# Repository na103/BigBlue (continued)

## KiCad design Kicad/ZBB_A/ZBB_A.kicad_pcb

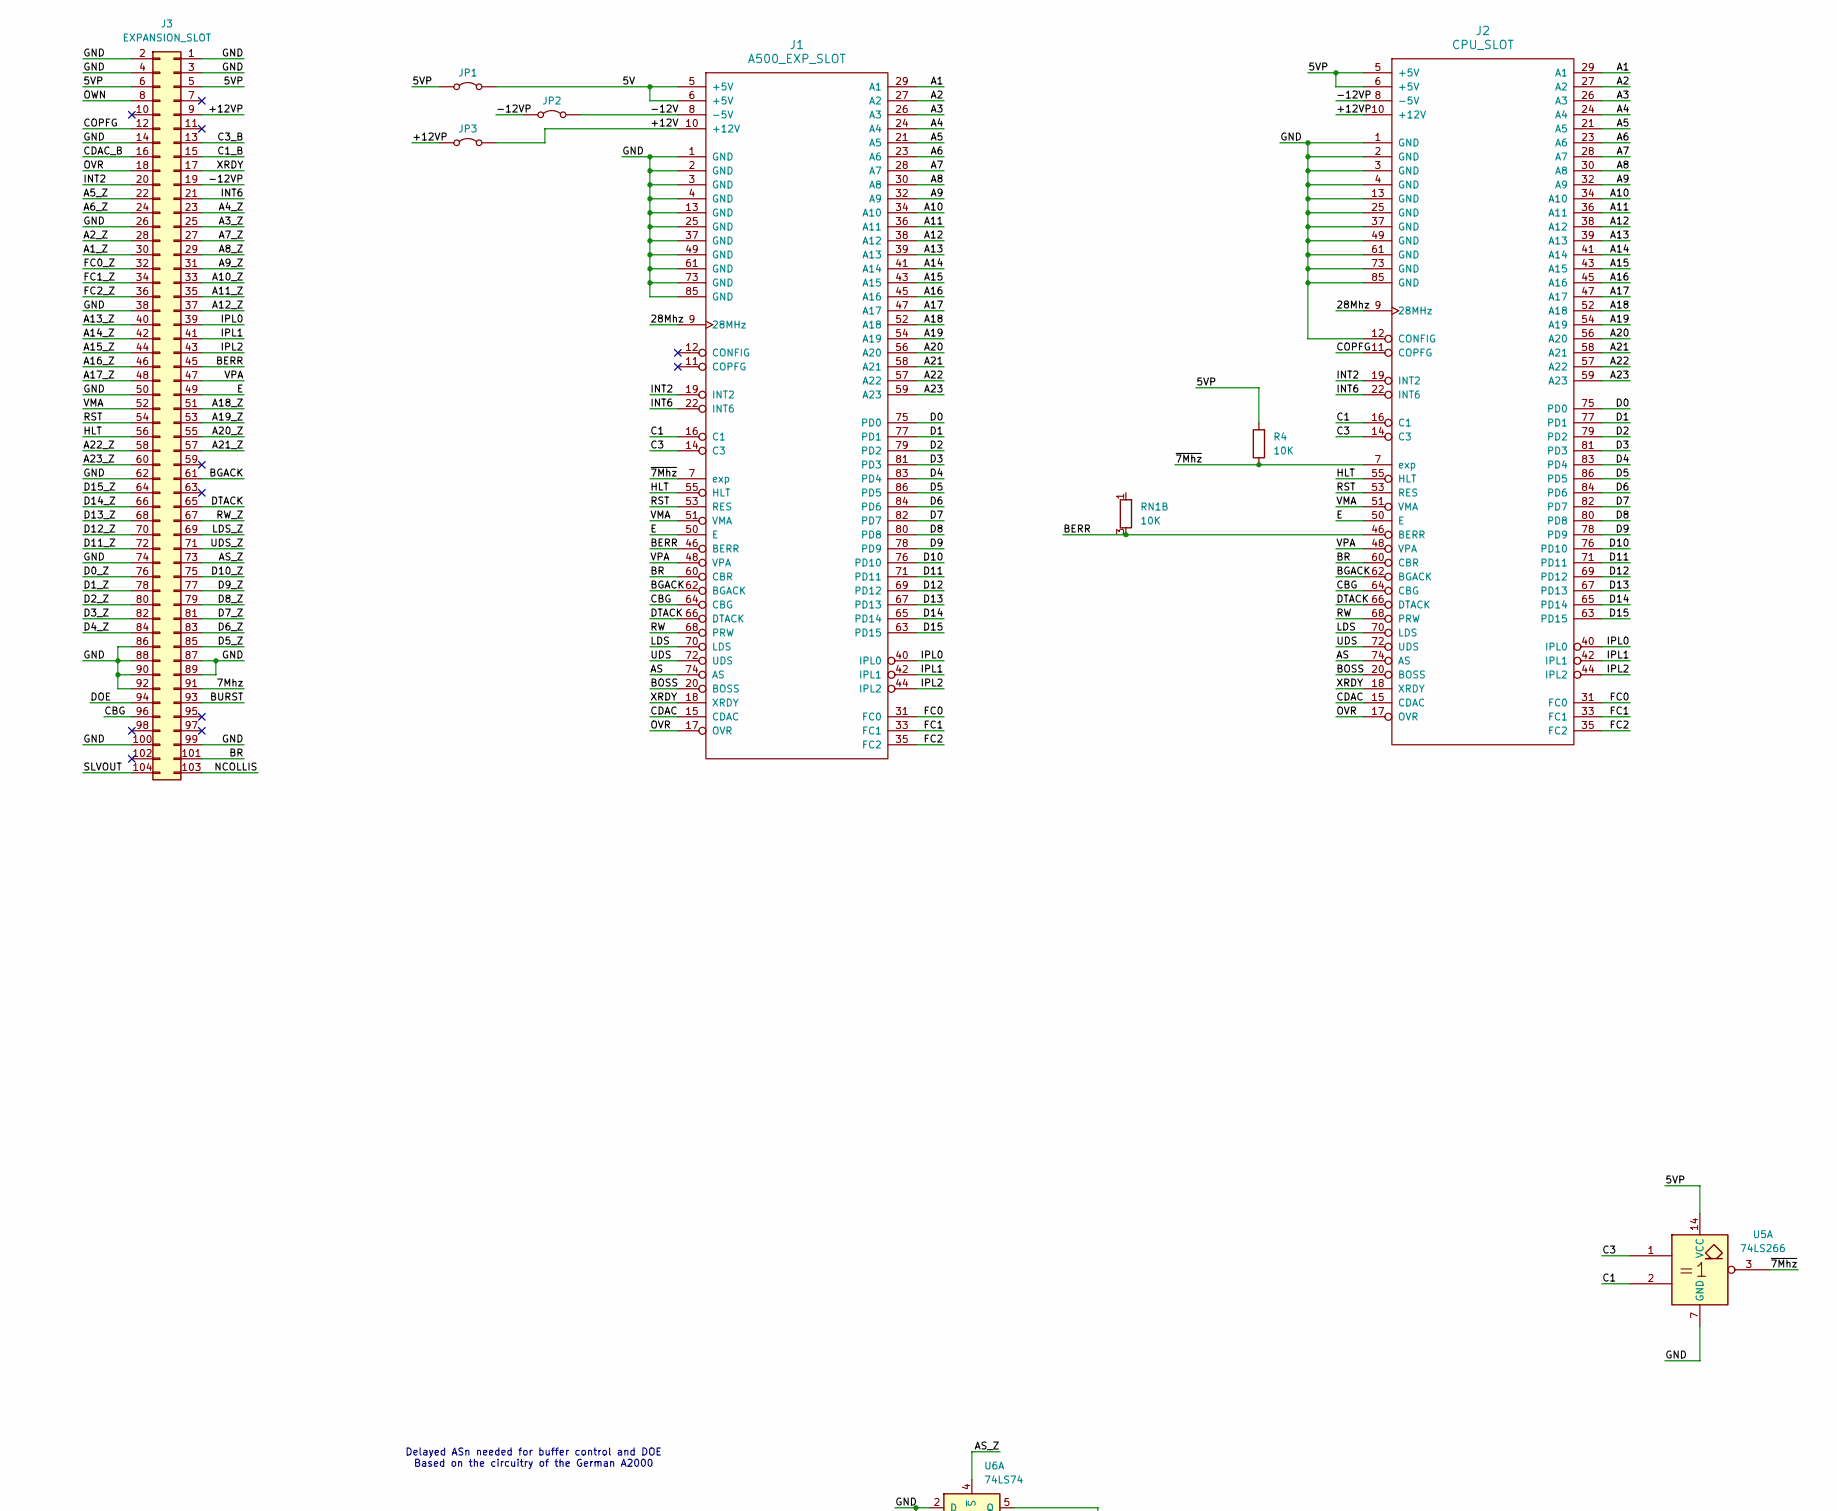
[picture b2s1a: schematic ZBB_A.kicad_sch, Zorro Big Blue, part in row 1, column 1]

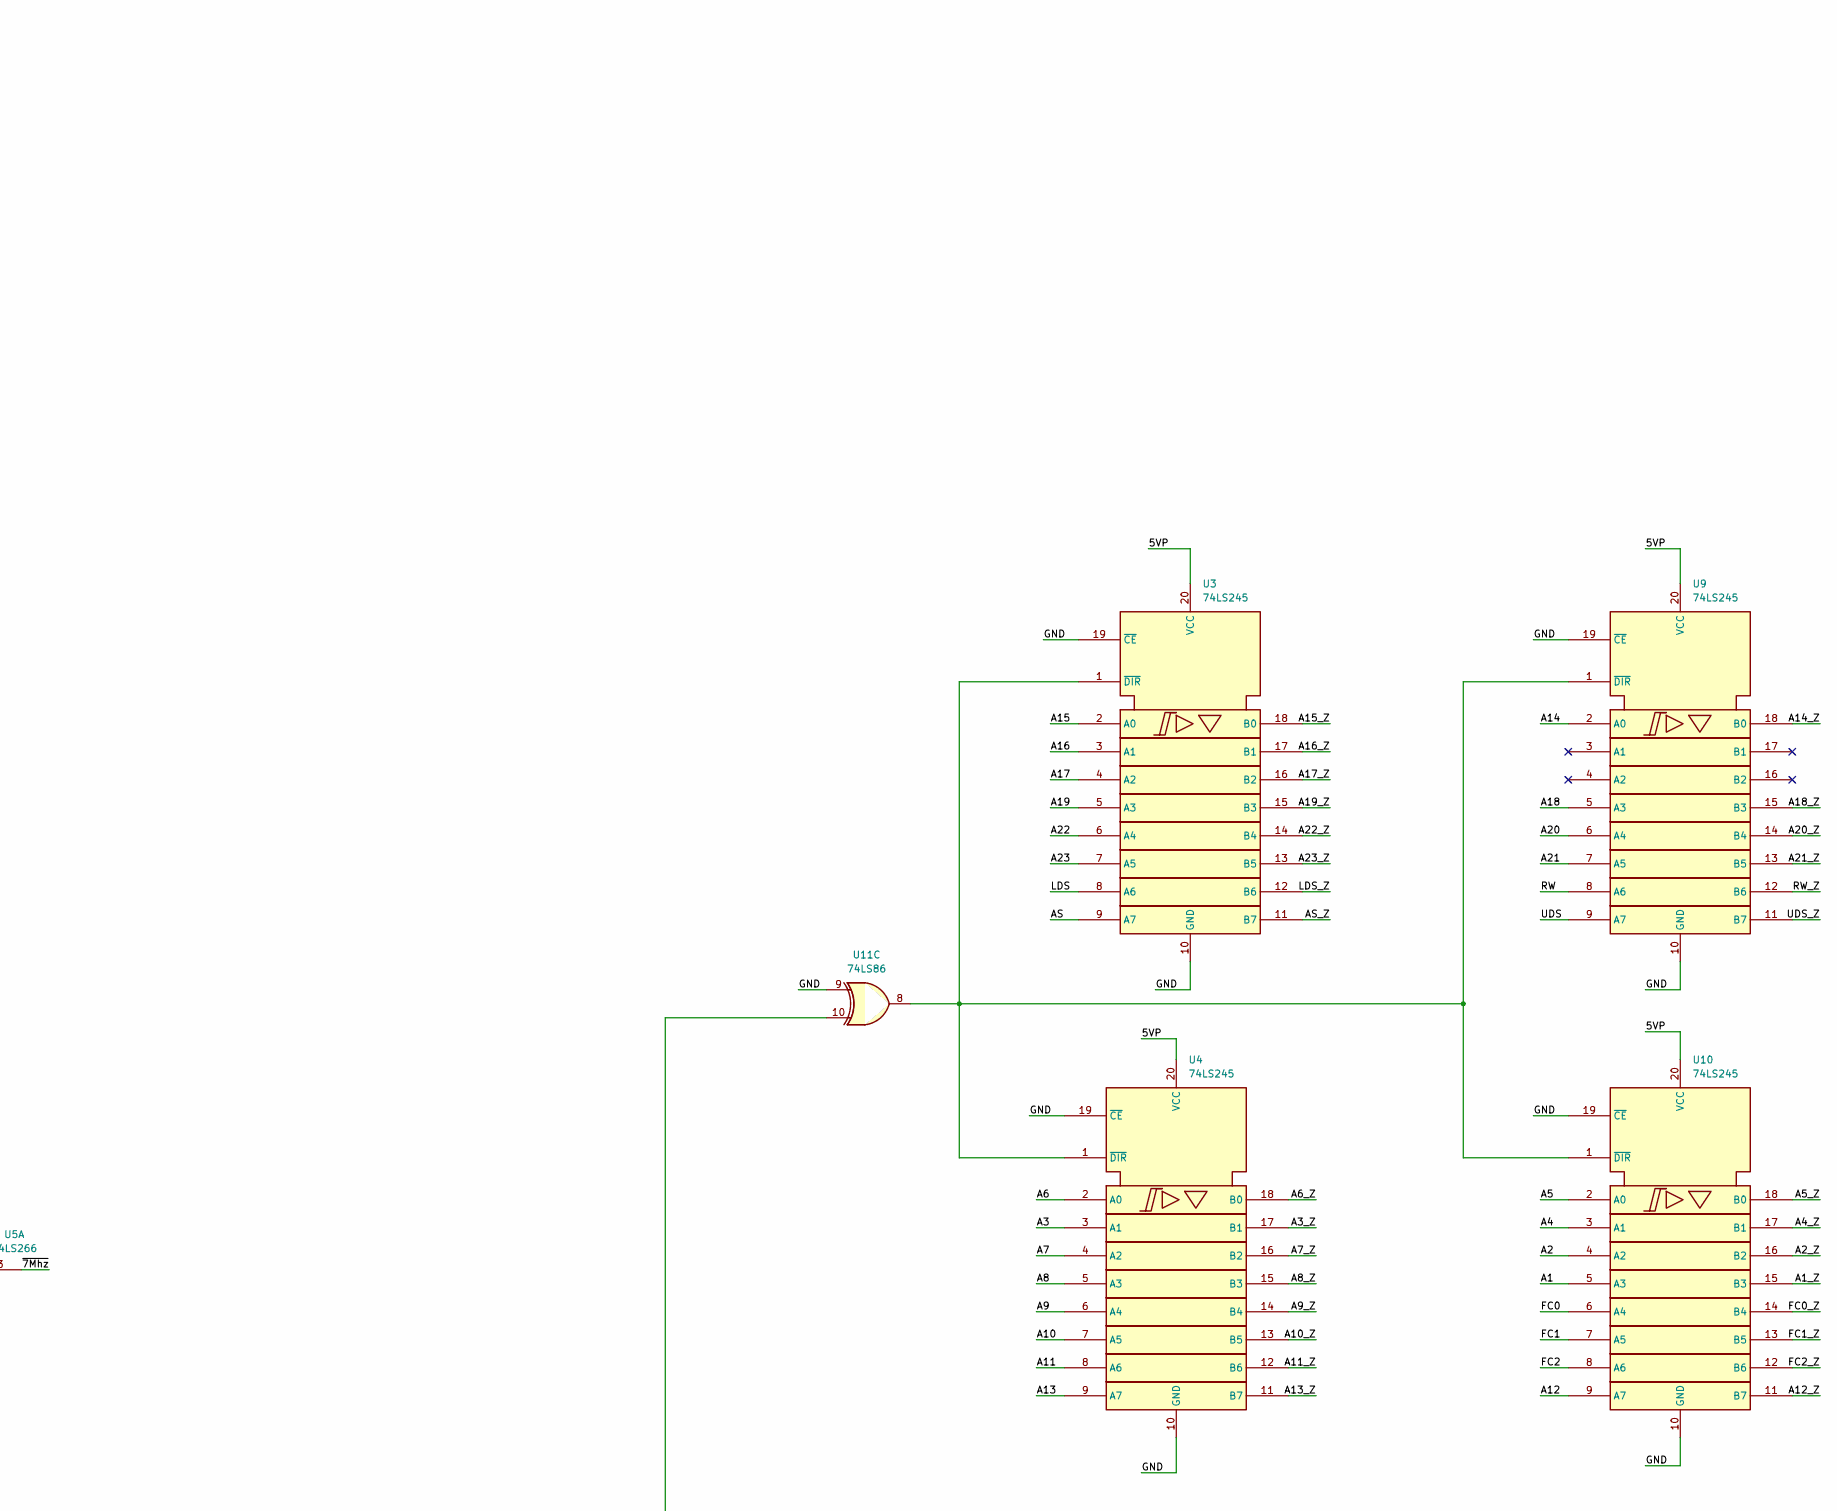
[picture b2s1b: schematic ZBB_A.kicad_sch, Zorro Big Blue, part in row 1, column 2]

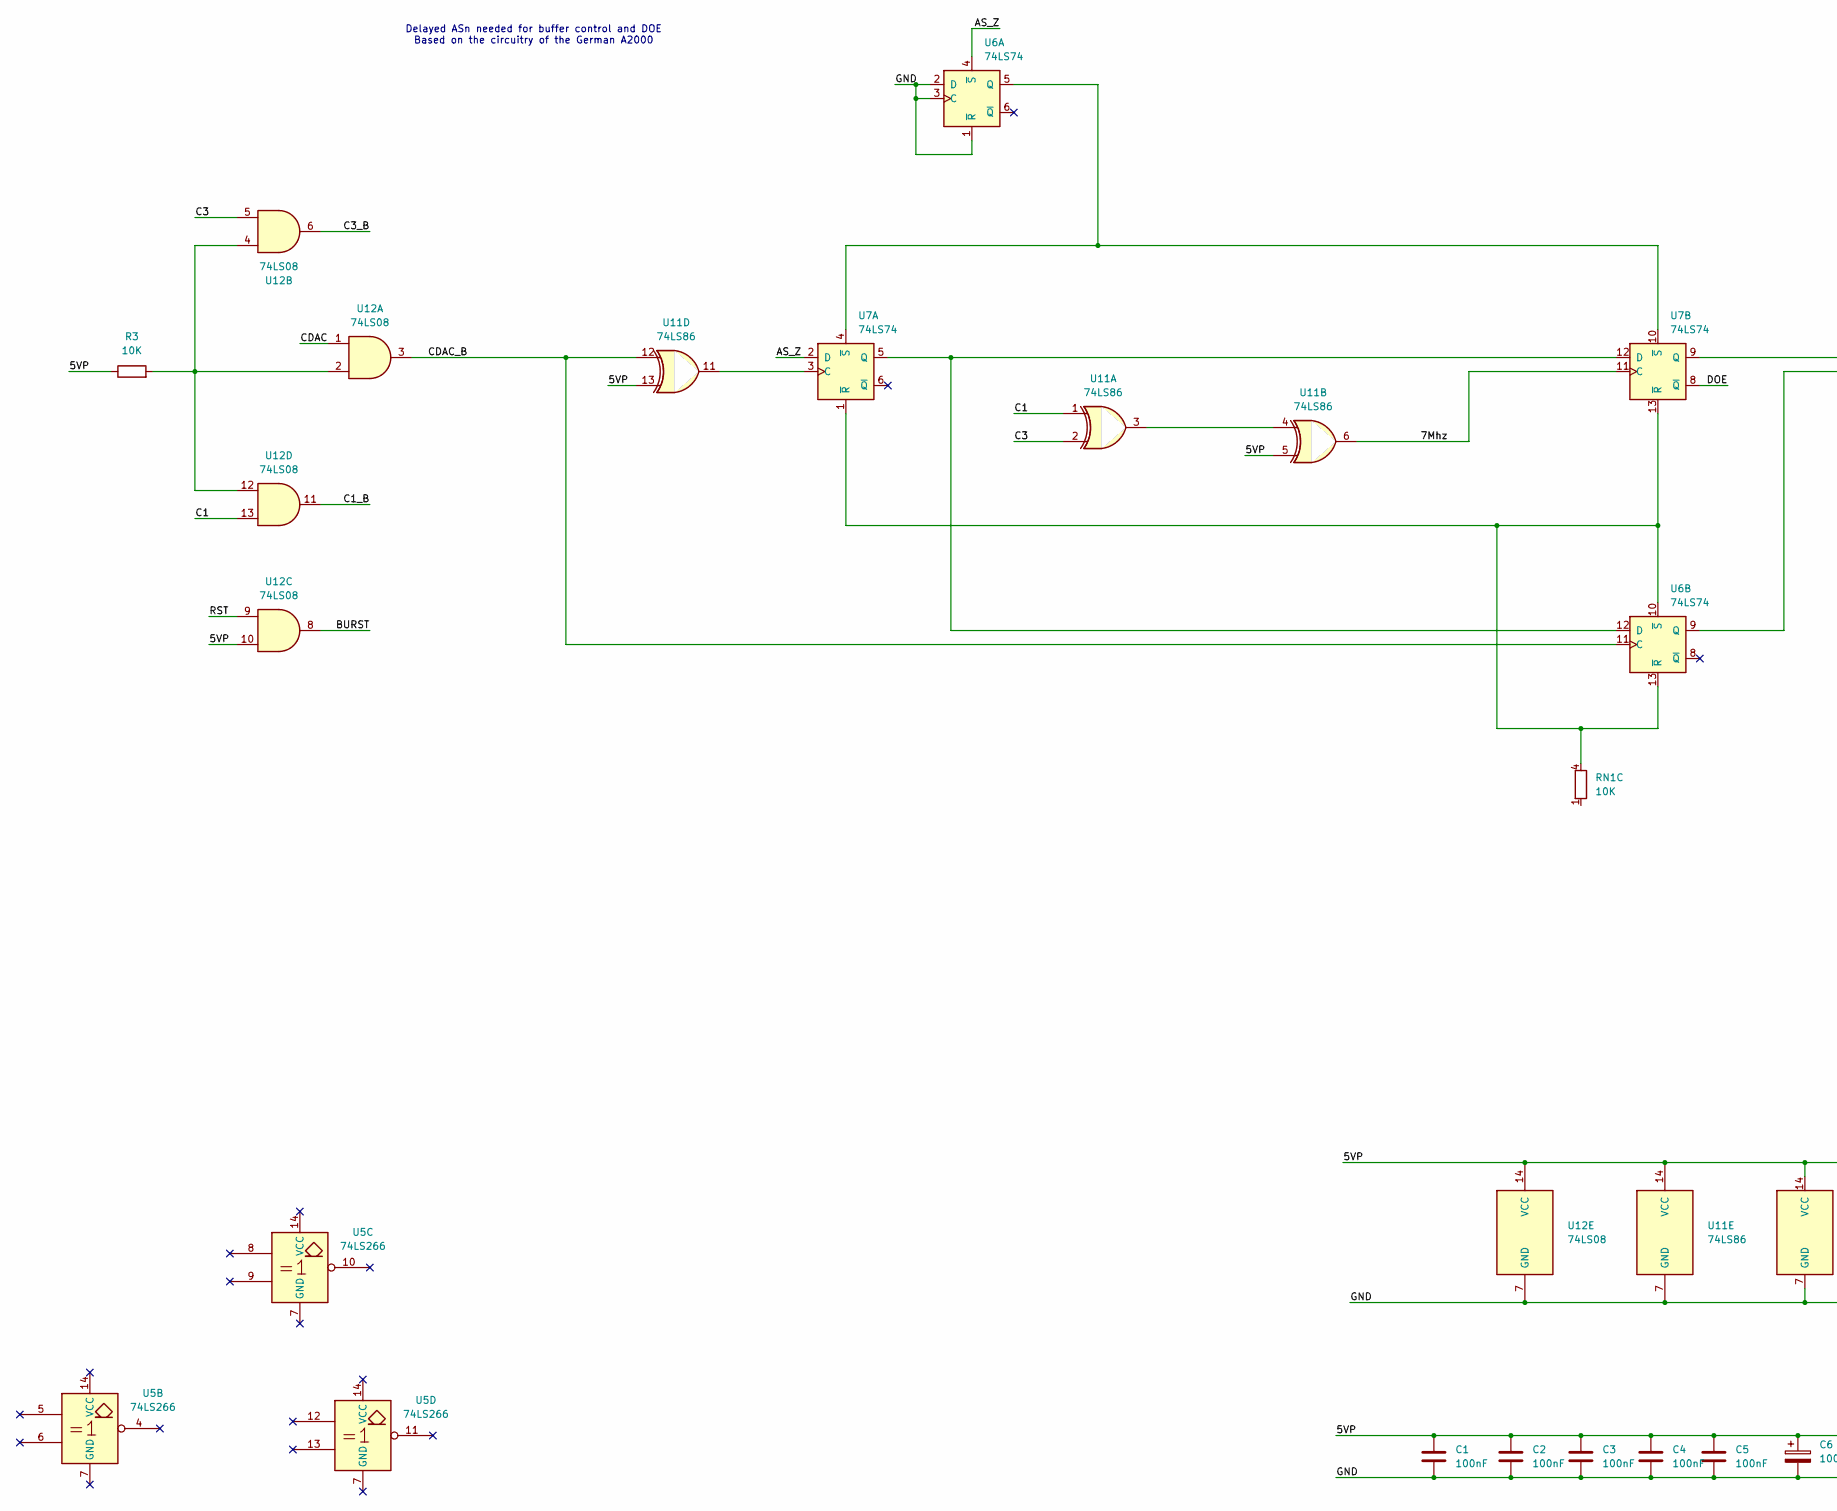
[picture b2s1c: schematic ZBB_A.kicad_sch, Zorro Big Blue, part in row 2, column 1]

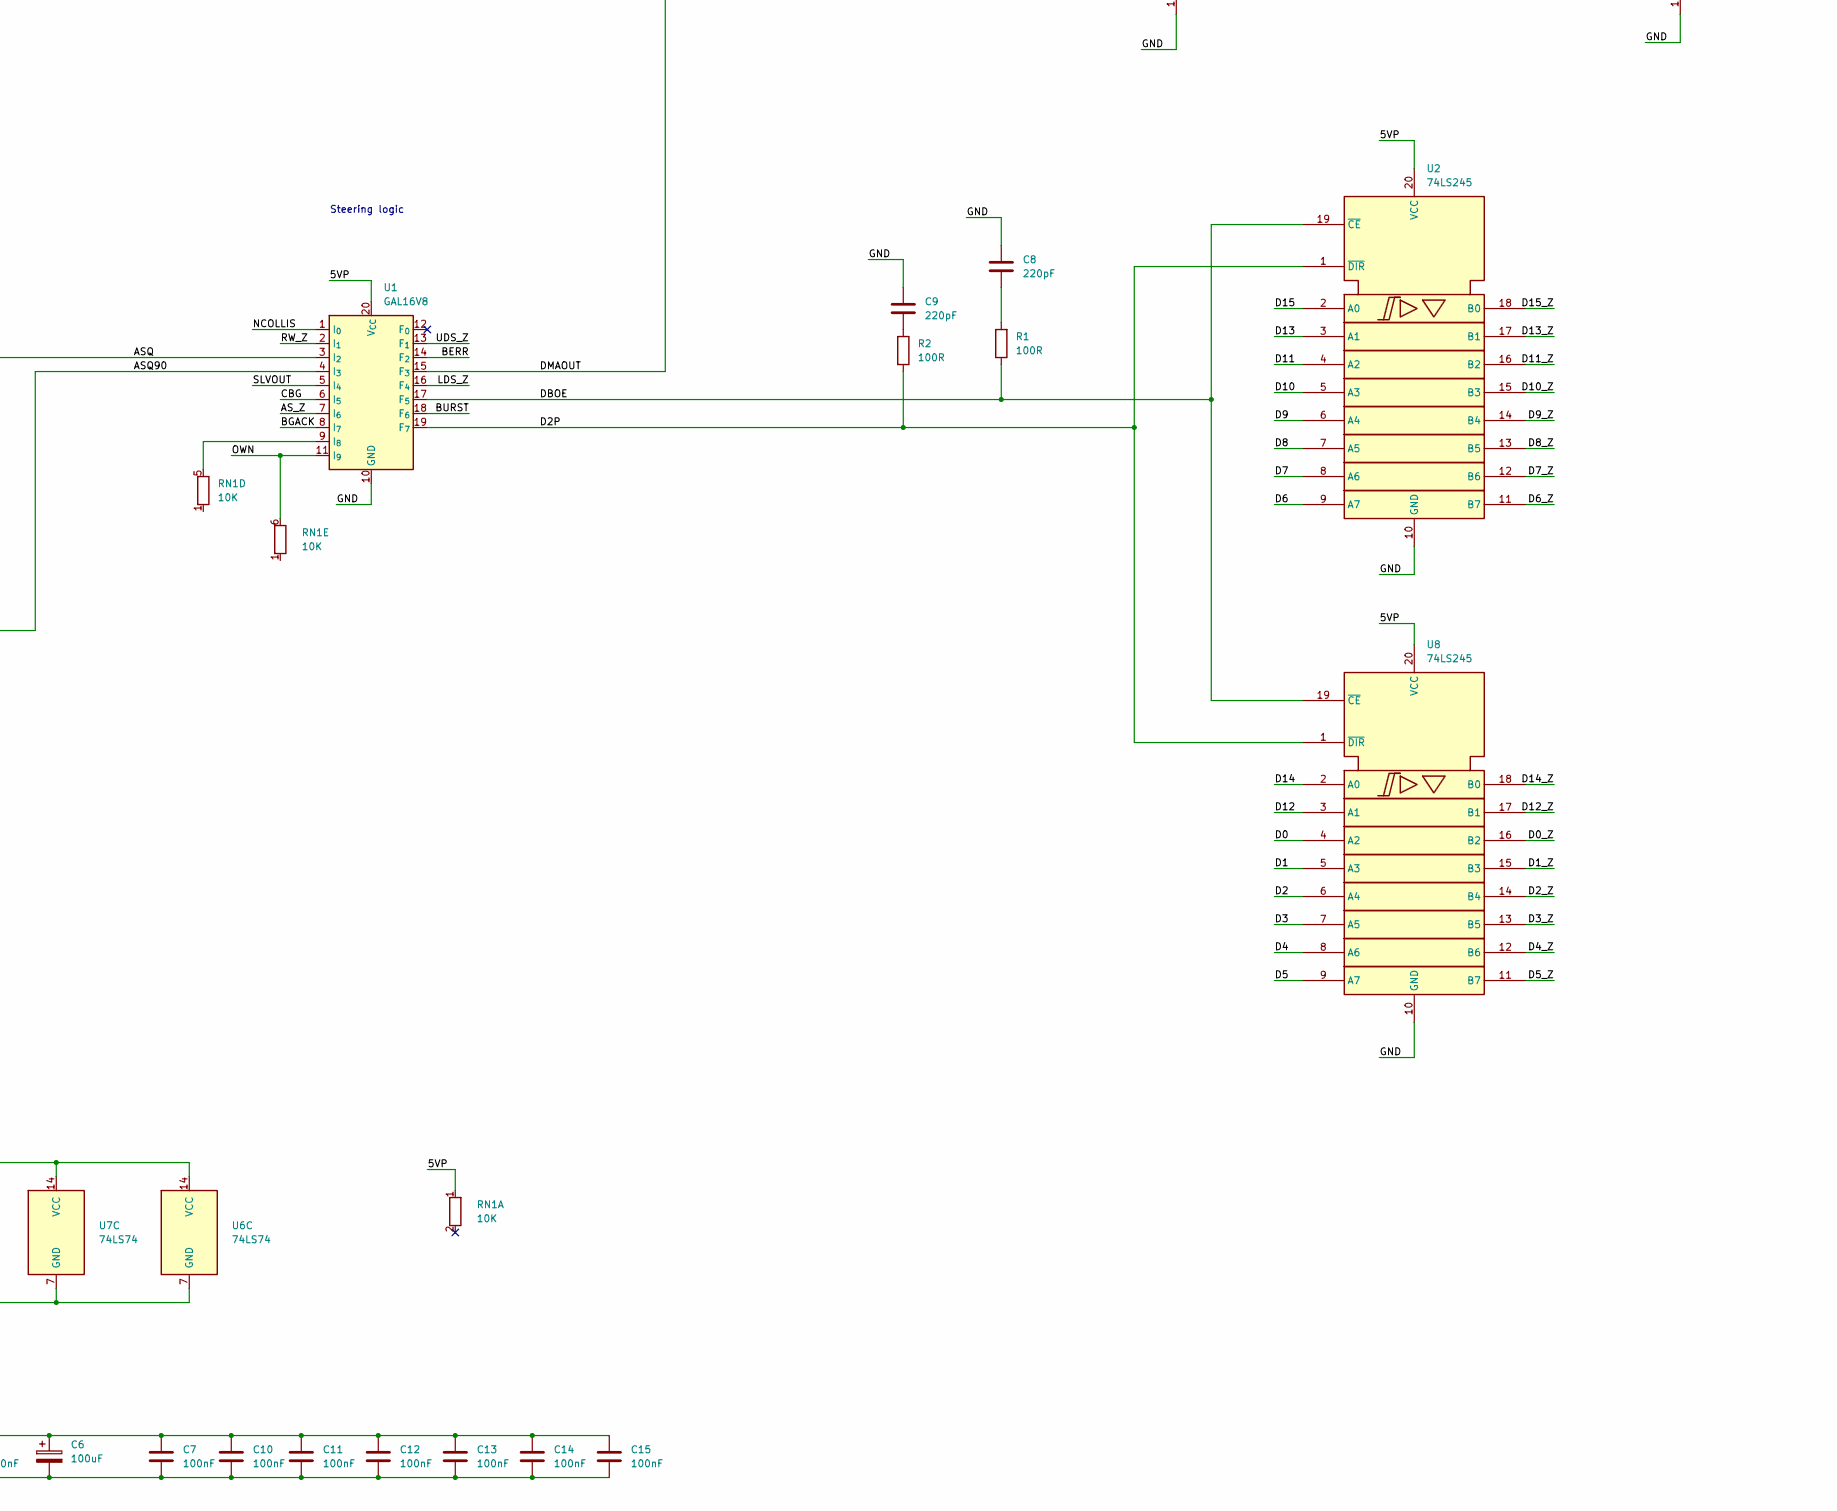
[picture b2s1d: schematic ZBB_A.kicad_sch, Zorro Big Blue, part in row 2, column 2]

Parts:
C1, C2, C3, C4, C5, C7, C10, C11, C12, C13, C14, C15: 100nF; C_Disc_D3.0mm_W1.6mm_P2.50mm
C6: 100uF; CP_Radial_D8.0mm_P3.50mm
C8, C9: 220pF; C_Disc_D3.0mm_W1.6mm_P2.50mm
J1: A500_EXP_SLOT; CPU Slot
J2: CPU_SLOT; CPU Slot
J3: EXPANSION_SLOT; PinHeader_2x52_P2.54mm_Vertical
JP1, JP2, JP3: Jumper_2_Bridged; PinHeader_1x02_P2.54mm_Vertical
R1, R2: 100R; R_Axial_DIN0204_L3.6mm_D1.6mm_P7.62mm_Horizontal
R3, R4: 10K; R_Axial_DIN0204_L3.6mm_D1.6mm_P7.62mm_Horizontal
RN1: 10K; R_Array_SIP6
U1: GAL16V8; DIP-20_W7.62mm
U2, U3, U4, U8, U9, U10: 74LS245; DIP-20_W7.62mm
U5: 74LS266; DIP-14_W7.62mm
U6, U7: 74LS74; DIP-14_W7.62mm
U11: 74LS86; DIP-14_W7.62mm
U12: 74LS08; DIP-14_W7.62mm

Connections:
/5V: J1.5 (+5V), J1.6 (+5V), JP1.2 (B)
/5VP: C1.2, C2.2, C3.2, C4.2, C5.1, C6.1, C7.2, C10.2, C11.2, C12.2, C13.2, C14.2, C15.1, J2.5 (+5V), J2.6 (+5V), J3.5, J3.6, JP1.1 (A), R3.1, R4.2, RN1.1 (R1), U1.20 (V_{CC}), U2.20 (VCC), U3.20 (VCC), U4.20 (VCC), U5.14 (VCC), U6.14 (VCC), U7.14 (VCC), U8.20 (VCC), U9.20 (VCC), U10.20 (VCC), U11.5, U11.13, U11.14 (VCC), U12.10, U12.14 (VCC)
/7Mhz: J3.91, U7.11 (C), U11.6
/28Mhz: J1.9 (28MHz), J2.9 (28MHz)
/+12V: J1.10 (+12V), JP3.2 (B)
/+12VP: J2.10 (+12V), J3.9, JP3.1 (A)
/-12V: J1.8 (-5V), JP2.2 (B)
/-12VP: J2.8 (-5V), J3.19, JP2.1 (A)
/A1: J1.29 (A1), J2.29 (A1), U10.5 (A3)
/A1_Z: J3.30, U10.15 (B3)
/A2: J1.27 (A2), J2.27 (A2), U10.4 (A2)
/A2_Z: J3.28, U10.16 (B2)
/A3: J1.26 (A3), J2.26 (A3), U4.3 (A1)
/A3_Z: J3.25, U4.17 (B1)
/A4: J1.24 (A4), J2.24 (A4), U10.3 (A1)
/A4_Z: J3.23, U10.17 (B1)
/A5: J1.21 (A5), J2.21 (A5), U10.2 (A0)
/A5_Z: J3.22, U10.18 (B0)
/A6: J1.23 (A6), J2.23 (A6), U4.2 (A0)
/A6_Z: J3.24, U4.18 (B0)
/A7: J1.28 (A7), J2.28 (A7), U4.4 (A2)
/A7_Z: J3.27, U4.16 (B2)
/A8: J1.30 (A8), J2.30 (A8), U4.5 (A3)
/A8_Z: J3.29, U4.15 (B3)
/A9: J1.32 (A9), J2.32 (A9), U4.6 (A4)
/A9_Z: J3.31, U4.14 (B4)
/A10: J1.34 (A10), J2.34 (A10), U4.7 (A5)
/A10_Z: J3.33, U4.13 (B5)
/A11: J1.36 (A11), J2.36 (A11), U4.8 (A6)
/A11_Z: J3.35, U4.12 (B6)
/A12: J1.38 (A12), J2.38 (A12), U10.9 (A7)
/A12_Z: J3.37, U10.11 (B7)
/A13: J1.39 (A13), J2.39 (A13), U4.9 (A7)
/A13_Z: J3.40, U4.11 (B7)
/A14: J1.41 (A14), J2.41 (A14), U9.2 (A0)
/A14_Z: J3.42, U9.18 (B0)
/A15: J1.43 (A15), J2.43 (A15), U3.2 (A0)
/A15_Z: J3.44, U3.18 (B0)
/A16: J1.45 (A16), J2.45 (A16), U3.3 (A1)
/A16_Z: J3.46, U3.17 (B1)
/A17: J1.47 (A17), J2.47 (A17), U3.4 (A2)
/A17_Z: J3.48, U3.16 (B2)
/A18: J1.52 (A18), J2.52 (A18), U9.5 (A3)
/A18_Z: J3.51, U9.15 (B3)
/A19: J1.54 (A19), J2.54 (A19), U3.5 (A3)
/A19_Z: J3.53, U3.15 (B3)
/A20: J1.56 (A20), J2.56 (A20), U9.6 (A4)
/A20_Z: J3.55, U9.14 (B4)
/A21: J1.58 (A21), J2.58 (A21), U9.7 (A5)
/A21_Z: J3.57, U9.13 (B5)
/A22: J1.57 (A22), J2.57 (A22), U3.6 (A4)
/A22_Z: J3.58, U3.14 (B4)
/A23: J1.59 (A23), J2.59 (A23), U3.7 (A5)
/A23_Z: J3.60, U3.13 (B5)
/AS: J1.74 (AS), J2.74 (AS), U3.9 (A7)
/ASQ: U1.3 (I_{2}), U7.9 (Q)
/ASQ90: U1.4 (I_{3}), U6.9 (Q)
/AS_Z: J3.73, U1.7 (I_{6}), U3.11 (B7), U6.4 (~S), U7.2 (D)
/BERR: J1.46 (BERR), J2.46 (BERR), J3.45, RN1.3 (R2.2), U1.14 (F_{2})
/BGACK: J1.62 (BGACK), J2.62 (BGACK), J3.61, U1.8 (I_{7})
/BOSS: J1.20 (BOSS), J2.20 (BOSS)
/BR: J1.60 (CBR), J2.60 (CBR), J3.101
/BURST: J3.93, U1.18 (F_{6}), U12.8
/C1: J1.16 (C1), J2.16 (C1), U5.2, U11.1, U12.13
/C1_B: J3.15, U12.11
/C3: J1.14 (C3), J2.14 (C3), U5.1, U11.2, U12.5
/C3_B: J3.13, U12.6
/CBG: J1.64 (CBG), J2.64 (CBG), J3.96, U1.6 (I_{5})
/CDAC: J1.15 (CDAC), J2.15 (CDAC), U12.1
/CDAC_B: J3.16, U6.11 (C), U11.12, U12.3
/COPFG: J2.11 (COPFG), J3.12
/D0: J1.75 (PD0), J2.75 (PD0), U8.4 (A2)
/D0_Z: J3.76, U8.16 (B2)
/D1: J1.77 (PD1), J2.77 (PD1), U8.5 (A3)
/D1_Z: J3.78, U8.15 (B3)
/D2: J1.79 (PD2), J2.79 (PD2), U8.6 (A4)
/D2P: R2.2, U1.19 (F_{7}), U2.1 (~DIR), U8.1 (~DIR)
/D2_Z: J3.80, U8.14 (B4)
/D3: J1.81 (PD3), J2.81 (PD3), U8.7 (A5)
/D3_Z: J3.82, U8.13 (B5)
/D4: J1.83 (PD4), J2.83 (PD4), U8.8 (A6)
/D4_Z: J3.84, U8.12 (B6)
/D5: J1.86 (PD5), J2.86 (PD5), U8.9 (A7)
/D5_Z: J3.85, U8.11 (B7)
/D6: J1.84 (PD6), J2.84 (PD6), U2.9 (A7)
/D6_Z: J3.83, U2.11 (B7)
/D7: J1.82 (PD7), J2.82 (PD7), U2.8 (A6)
/D7_Z: J3.81, U2.12 (B6)
/D8: J1.80 (PD8), J2.80 (PD8), U2.7 (A5)
/D8_Z: J3.79, U2.13 (B5)
/D9: J1.78 (PD9), J2.78 (PD9), U2.6 (A4)
/D9_Z: J3.77, U2.14 (B4)
/D10: J1.76 (PD10), J2.76 (PD10), U2.5 (A3)
/D10_Z: J3.75, U2.15 (B3)
/D11: J1.71 (PD11), J2.71 (PD11), U2.4 (A2)
/D11_Z: J3.72, U2.16 (B2)
/D12: J1.69 (PD12), J2.69 (PD12), U8.3 (A1)
/D12_Z: J3.70, U8.17 (B1)
/D13: J1.67 (PD13), J2.67 (PD13), U2.3 (A1)
/D13_Z: J3.68, U2.17 (B1)
/D14: J1.65 (PD14), J2.65 (PD14), U8.2 (A0)
/D14_Z: J3.66, U8.18 (B0)
/D15: J1.63 (PD15), J2.63 (PD15), U2.2 (A0)
/D15_Z: J3.64, U2.18 (B0)
/DBOE: R1.1, U1.17 (F_{5}), U2.19 (~CE), U8.19 (~CE)
/DMAOUT: U1.15 (F_{3}), U11.10
/DOE: J3.94, U7.8 (~Q)
/DTACK: J1.66 (DTACK), J2.66 (DTACK), J3.65
/E: J1.50 (E), J2.50 (E), J3.49
/FC0: J1.31 (FC0), J2.31 (FC0), U10.6 (A4)
/FC0_Z: J3.32, U10.14 (B4)
/FC1: J1.33 (FC1), J2.33 (FC1), U10.7 (A5)
/FC1_Z: J3.34, U10.13 (B5)
/FC2: J1.35 (FC2), J2.35 (FC2), U10.8 (A6)
/FC2_Z: J3.36, U10.12 (B6)
/GND: C1.1, C2.1, C3.1, C4.1, C5.2, C6.2, C7.1, C8.1, C9.2, C10.1, C11.1, C12.1, C13.1, C14.1, C15.2, J1.1 (GND), J1.2 (GND), J1.3 (GND), J1.4 (GND), J1.13 (GND), J1.25 (GND), J1.37 (GND), J1.49 (GND), J1.61 (GND), J1.73 (GND), J1.85 (GND), J2.1 (GND), J2.2 (GND), J2.3 (GND), J2.4 (GND), J2.12 (CONFIG), J2.13 (GND), J2.25 (GND), J2.37 (GND), J2.49 (GND), J2.61 (GND), J2.73 (GND), J2.85 (GND), J3.1, J3.2, J3.3, J3.4, J3.14, J3.26, J3.38, J3.50, J3.62, J3.74, J3.86, J3.87, J3.88, J3.89, J3.90, J3.92, J3.99, J3.100, U1.10 (GND), U2.10 (GND), U3.10 (GND), U3.19 (~CE), U4.10 (GND), U4.19 (~CE), U5.7 (GND), U6.1 (~R), U6.2 (D), U6.3 (C), U6.7 (GND), U7.7 (GND), U8.10 (GND), U9.10 (GND), U9.19 (~CE), U10.10 (GND), U10.19 (~CE), U11.7 (GND), U11.9, U12.7 (GND)
/HLT: J1.55 (HLT), J2.55 (HLT), J3.56
/INT2: J1.19 (INT2), J2.19 (INT2), J3.20
/INT6: J1.22 (INT6), J2.22 (INT6), J3.21
/IPL0: J1.40 (IPL0), J2.40 (IPL0), J3.39
/IPL1: J1.42 (IPL1), J2.42 (IPL1), J3.41
/IPL2: J1.44 (IPL2), J2.44 (IPL2), J3.43
/LDS: J1.70 (LDS), J2.70 (LDS), U3.8 (A6)
/LDS_Z: J3.69, U1.16 (F_{4}), U3.12 (B6)
/NCOLLIS: J3.103, U1.1 (I_{0})
/OVR: J1.17 (OVR), J2.17 (OVR), J3.18
/OWN: J3.8, RN1.6 (R5.2), U1.11 (I_{9})
/RST: J1.53 (RES), J2.53 (RES), J3.54, U12.9
/RW: J1.68 (PRW), J2.68 (PRW), U9.8 (A6)
/RW_Z: J3.67, U1.2 (I_{1}), U9.12 (B6)
/SLVOUT: J3.104, U1.5 (I_{4})
/UDS: J1.72 (UDS), J2.72 (UDS), U9.9 (A7)
/UDS_Z: J3.71, U1.13 (F_{1}), U9.11 (B7)
/VMA: J1.51 (VMA), J2.51 (VMA), J3.52
/VPA: J1.48 (VPA), J2.48 (VPA), J3.47
/XRDY: J1.18 (XRDY), J2.18 (XRDY), J3.17
/~7Mhz: J1.7 (exp), J2.7 (exp), R4.1, U5.3
unnamed: C8.2, R1.2
unnamed: C9.1, R2.1
unnamed: R3.2, U12.2, U12.4, U12.12
unnamed: RN1.4 (R3.2), U6.10 (~S), U6.13 (~R), U7.1 (~R), U7.13 (~R)
unnamed: RN1.5 (R4.2), U1.9 (I_{8})
unnamed: U6.5 (Q), U7.4 (~S), U7.10 (~S)
unnamed: U6.12 (D), U7.5 (Q), U7.12 (D)
unnamed: U7.3 (C), U11.11
unnamed: U3.1 (~DIR), U4.1 (~DIR), U9.1 (~DIR), U10.1 (~DIR), U11.8
unnamed: U11.3, U11.4

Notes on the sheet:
Steering logic
Delayed ASn needed for buffer control and DOE Based on the circuitry of the German A2000

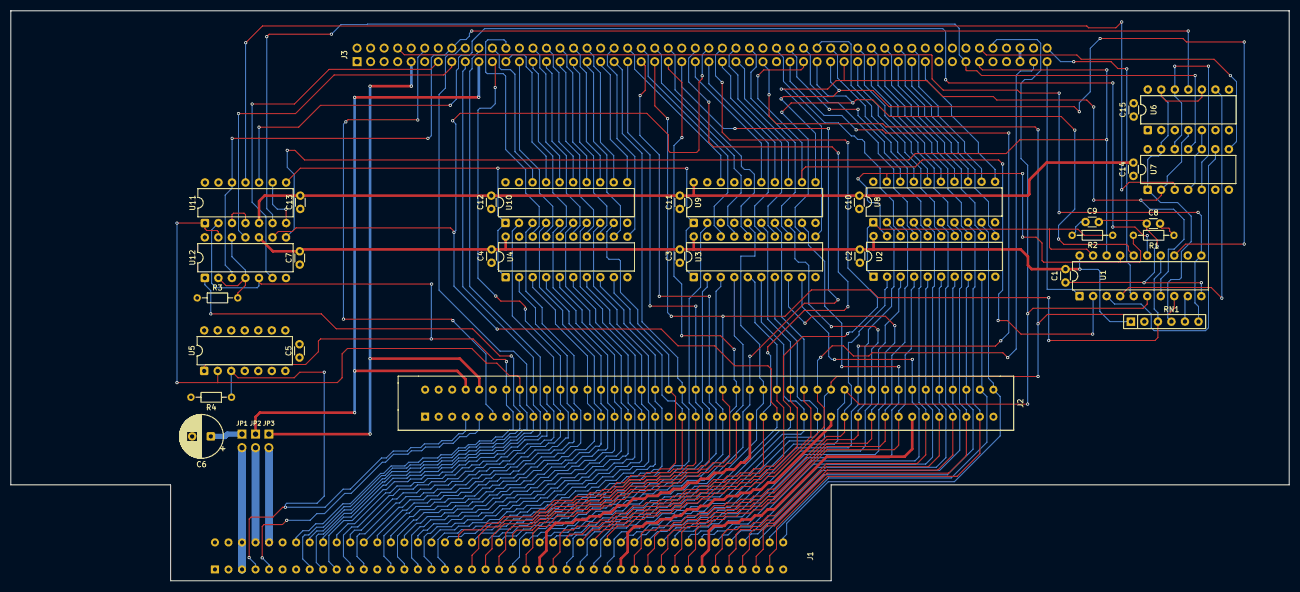
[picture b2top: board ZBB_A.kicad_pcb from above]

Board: 4 copper layers, 240.0 x 107.0 mm, 38 parts (0 on the bottom side), 147 nets.

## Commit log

2026-05-22 license file
2026-05-22 Misc review
2026-05-22 BigBlue Images
2026-05-22 Dupal dump
2026-05-22 BigBlue Kicad remake
2026-05-22 PAL reverse and C= docs
2026-05-22 README update
